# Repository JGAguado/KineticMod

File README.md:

[![GitHub Release][releases-shield]][releases]
[![License][license-shield]](LICENSE)

[![Project Maintenance][maintenance-shield]][maintenance]
[![BuyMeCoffee][buymecoffee-shield]][buymecoffee]

# KineticMod
Mod for ArduLab, directly plugable via the Mod Interface. The KineticMod is designed to enhance the ArduLab functions applied to control multiple motors by PWM such as servos.

## Project tree

<li><a href="./Design/">Design</a></li>
<li><a href="./Documentation/">Documentation</a></li>

<li><a href="./README.md">README.md</a></li>

[releases-shield]: https://img.shields.io/github/release/JGAguado/KineticMod.svg?style=for-the-badge
[releases]: https://github.com/JGAguado/KineticMod/releases

[license-shield]: https://img.shields.io/badge/License-CC%20BY--NC--SA%204.0-lightgrey.svg?style=for-the-badge

[maintenance-shield]: https://img.shields.io/badge/maintainer-J.%20G.%20Aguado-blue.svg?style=for-the-badge
[maintenance]: https://github.com/JGAguado

[buymecoffee-shield]: https://img.shields.io/badge/buy%20me%20a%20coffee-support-yellow.svg?style=for-the-badge
[buymecoffee]: https://www.buymeacoffee.com/J.G.Aguado

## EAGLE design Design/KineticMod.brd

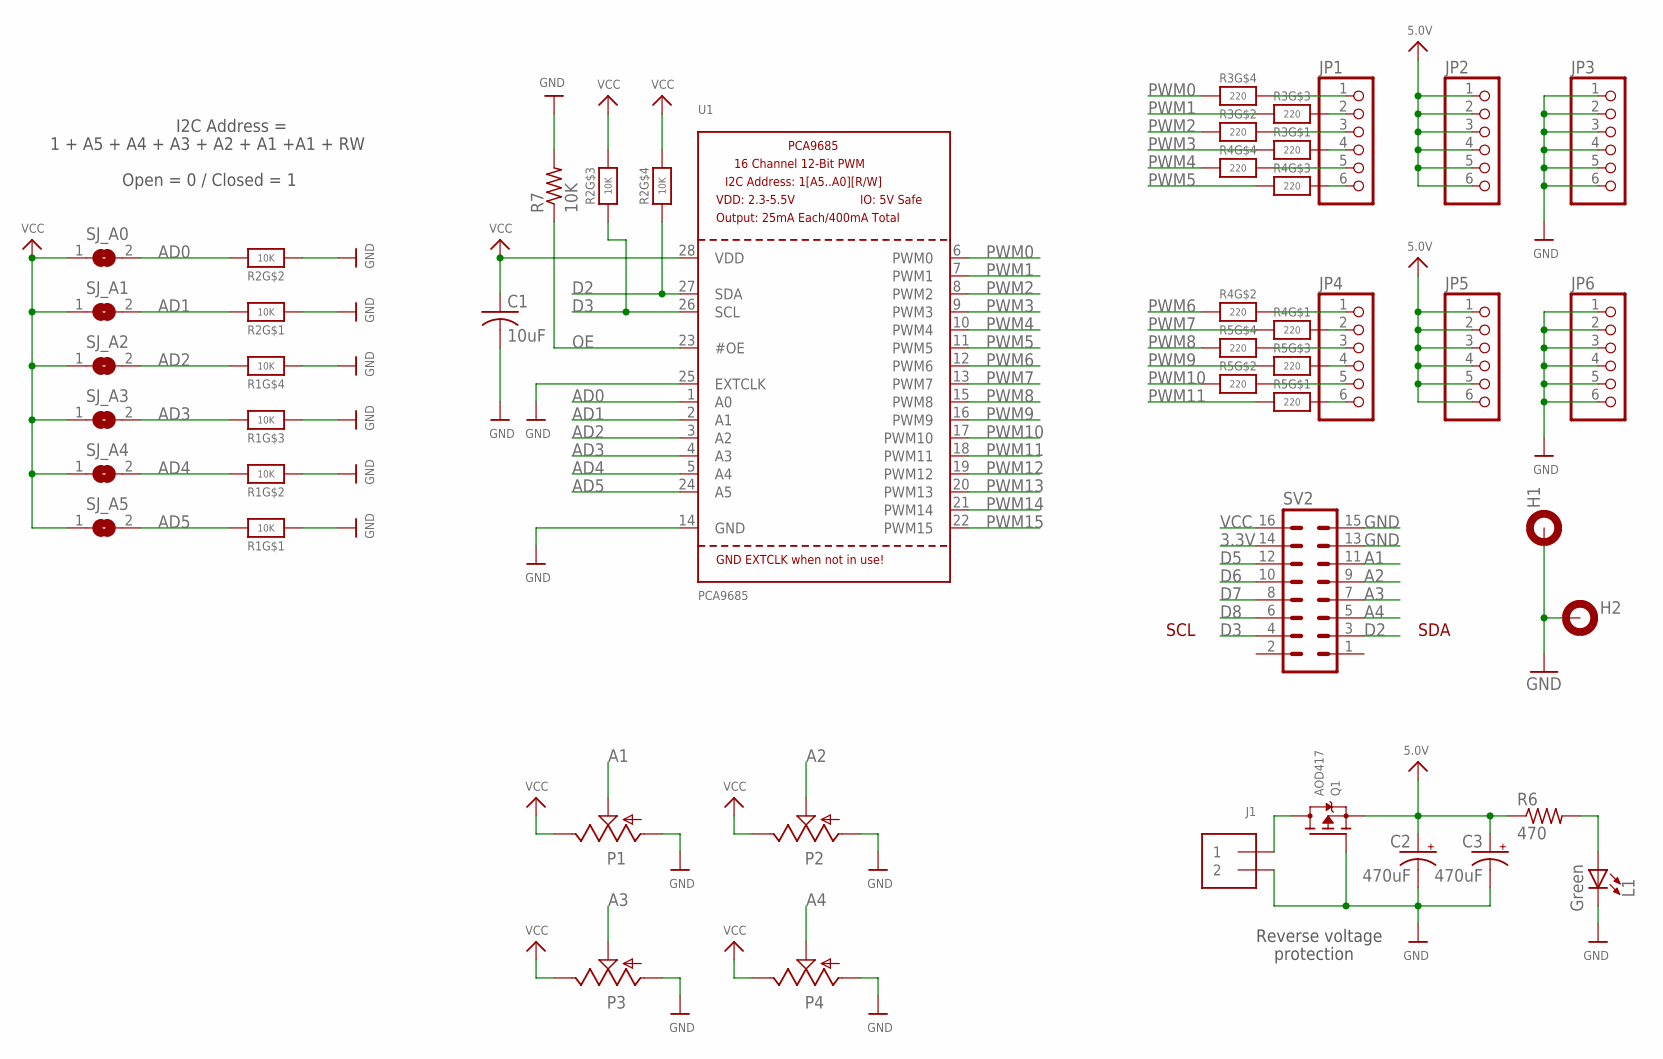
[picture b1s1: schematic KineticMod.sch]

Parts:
C1: 10uF; 1206
C2, C3: 470uF; D/7343-31R
H1, H2: MOUNT-PAD-ROUND3.2; 3,2-PAD
J1: TERMBLOCK_1X2; TERMBLOCK_1X2-3.5MM
JP1, JP2, JP3, JP4, JP5, JP6: PINHD-1X6; 1X06
L1: Green; LED1206
P1, P2, P3, P4: ALPS_RK09K_VERTICAL
Q1: AOD417; TO252
R1, R2: 10K; RESPACK_4X0603
R3, R4, R5: 220; RESPACK_4X0603
R6: 470; 1206
R7: 10K; 1206
SJ_A0, SJ_A1, SJ_A2, SJ_A3, SJ_A4, SJ_A5: SOLDERJUMPERREFLOW_NOPASTE; SOLDERJUMPER_REFLOW_NOPASTE
SV2: MA08-2
U1: PCA9685; TSSOP28

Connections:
3.3V: SV2.14
5.0V: C2.+, C3.+, JP2.1, JP2.2, JP2.3, JP2.4, JP2.5, JP2.6, JP5.1, JP5.2, JP5.3, JP5.4, JP5.5, JP5.6, Q1.2 (S), R6.1
A1: P1.2, SV2.11
A2: P2.2, SV2.9
A3: P3.2, SV2.7
A4: P4.2, SV2.5
AD0: R2.7 (2), SJ_A0.2, U1.1 (A0)
AD1: R2.8 (2), SJ_A1.2, U1.2 (A1)
AD2: R1.5 (2), SJ_A2.2, U1.3 (A2)
AD3: R1.6 (2), SJ_A3.2, U1.4 (A3)
AD4: R1.7 (2), SJ_A4.2, U1.5 (A4)
AD5: R1.8 (2), SJ_A5.2, U1.24 (A5)
D2: R2.4 (1), SV2.3, U1.27 (SDA)
D3: R2.3 (1), SV2.4, U1.26 (SCL)
D5: SV2.12
D6: SV2.10
D7: SV2.8
D8: SV2.6
GND: C1.2, C2.-, C3.-, H1.B3,2, H2.B3,2, J1.2, JP3.1, JP3.2, JP3.3, JP3.4, JP3.5, JP3.6, JP6.1, JP6.2, JP6.3, JP6.4, JP6.5, JP6.6, L1.C, P1.1, P2.1, P3.1, P4.1, Q1.1 (G), R1.1, R1.2 (1), R1.3 (1), R1.4 (1), R2.1, R2.2 (1), R7.2, SV2.13, SV2.15, U1.14 (GND), U1.25 (EXTCLK)
unnamed: L1.A, R6.2
unnamed: JP4.1, R4.7 (2)
unnamed: JP4.2, R4.8 (2)
unnamed: JP1.6, R4.6 (2)
unnamed: JP1.5, R4.5 (2)
unnamed: JP1.4, R3.8 (2)
unnamed: JP1.3, R3.7 (2)
unnamed: JP1.2, R3.6 (2)
unnamed: JP1.1, R3.5 (2)
unnamed: JP4.3, R5.5 (2)
unnamed: JP4.4, R5.6 (2)
unnamed: JP4.5, R5.7 (2)
unnamed: JP4.6, R5.8 (2)
OE: R7.1, U1.23 (#OE)
PWM0: R3.4 (1), U1.6 (PWM0)
PWM1: R3.3 (1), U1.7 (PWM1)
PWM2: R3.2 (1), U1.8 (PWM2)
PWM3: R3.1, U1.9 (PWM3)
PWM4: R4.4 (1), U1.10 (PWM4)
PWM5: R4.3 (1), U1.11 (PWM5)
PWM6: R4.2 (1), U1.12 (PWM6)
PWM7: R4.1, U1.13 (PWM7)
PWM8: R5.4 (1), U1.15 (PWM8)
PWM9: R5.3 (1), U1.16 (PWM9)
PWM10: R5.2 (1), U1.17 (PWM10)
PWM11: R5.1, U1.18 (PWM11)
PWM12: U1.19 (PWM12)
PWM13: U1.20 (PWM13)
PWM14: U1.21 (PWM14)
PWM15: U1.22 (PWM15)
PWRIN: J1.1, Q1.3 (D)
VCC: C1.1, P1.3, P2.3, P3.3, P4.3, R2.5 (2), R2.6 (2), SJ_A0.1, SJ_A1.1, SJ_A2.1, SJ_A3.1, SJ_A4.1, SJ_A5.1, SV2.16, U1.28 (VDD)

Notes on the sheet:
SCL
SDA
Reverse voltage
protection
1 + A5 + A4 + A3 + A2 + A1 +A1 + RW
I2C Address =
Open = 0 / Closed = 1

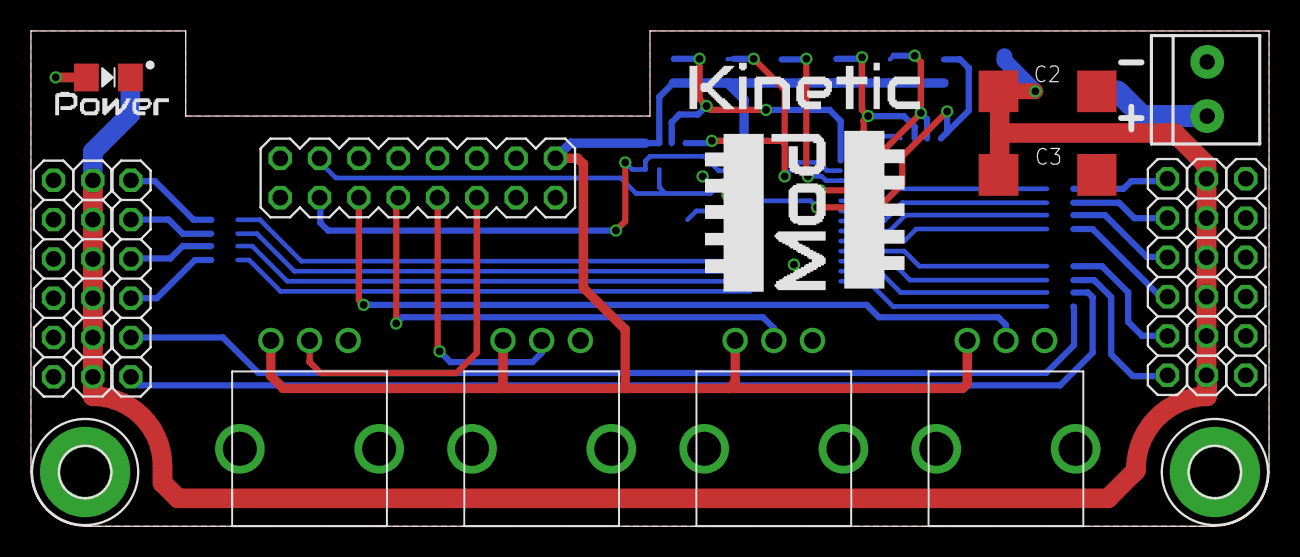
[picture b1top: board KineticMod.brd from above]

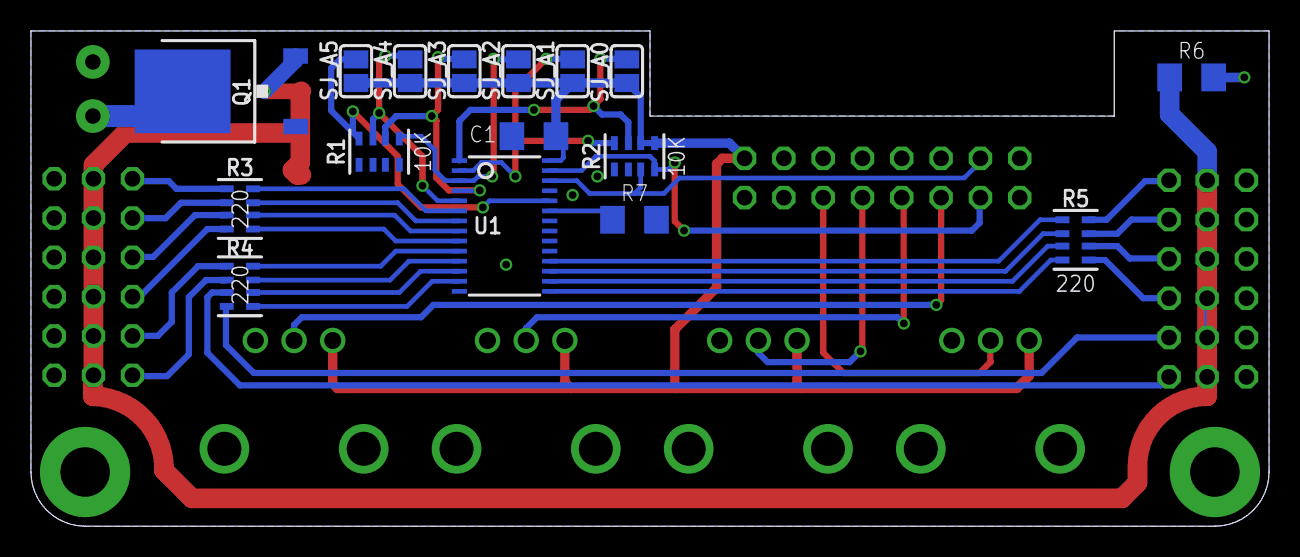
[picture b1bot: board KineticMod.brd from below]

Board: 2 copper layers, 80.0 x 32.0 mm, 33 parts (16 on the bottom side), 42 nets.

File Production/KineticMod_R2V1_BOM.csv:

No.,Design Ref,Description,Value,Package,Qty,Notes
1,C1,Capacitor,10 uF,C1206,1,
2,C2,Polarized capacitor,1000 uF,7343,1,Mouser No: 581-TAJE108M006RNJ
3,L1,Led,Green,1206,1,
4,Q1,Mosfet P-CH 30V,AOD417,TO252,1,https://www.digikey.es/product-detail/es/alpha-omega-semicon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
5,"R1, R2",Resistor array 4 resistor,10K,603,2,Mouser No: 667-EXB-38V103JV
6,"R3, R4, R5",Resistor array 4 resistor,220,603,3,Mouser No: 667-EXB-38V221JV
7,R6,Resistor,470,R1206,1,
8,R7,Resistor,10K,R1206,1,
9,SV1,"Pin header 2,54 - Right Angle",SFH11-PBPC-D08-RA-BK,,1,Sullins Part No: SFH11-PBPC-D08-RA-BK
10,U1,Controlador IC 16 Salida Lineal PWM,PCA9685,TSSOP28,1,
11,"JP1, JP2","Pin header 2,54 - Vertical",1x6,Black,2,"Soldered on Top layer in the column ""-"""
12,"JP3, JP4","Pin header 2,54 - Vertical",1x6,Red,2,"Soldered on Top layer in the column ""+"""
13,"JP5, JP6","Pin header 2,54 - Vertical",1x6,Yellow,2,"Soldered on Top layer in the column ""S"""
14,JP7,Terminal block 3.5mm,1x2,Through Hole,1,https://www.digikey.com/product-detail/en/amphenol-anytek/T5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
,,,,,,
,,,,,,
,,,,,,
,,,,,12,

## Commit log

2018-04-30 Initial commit KineticMod. Added SCH and BRD files
2018-05-02 Set theme jekyll-theme-cayman
2020-01-23 Updated KineticMod
2020-02-28 Updated capacitors: - C2 replaced by 470uF 2917 (7343) - Added C3 470uF 2917 (7343)
    Updated silkscreen
2020-02-28 Silkscreen original
2020-05-10 Updated Hardware design
2020-05-10 Updated Documentation
2020-05-10 Update silkscreens
2020-05-10 Updated Production files
2022-04-15 Updated structure
